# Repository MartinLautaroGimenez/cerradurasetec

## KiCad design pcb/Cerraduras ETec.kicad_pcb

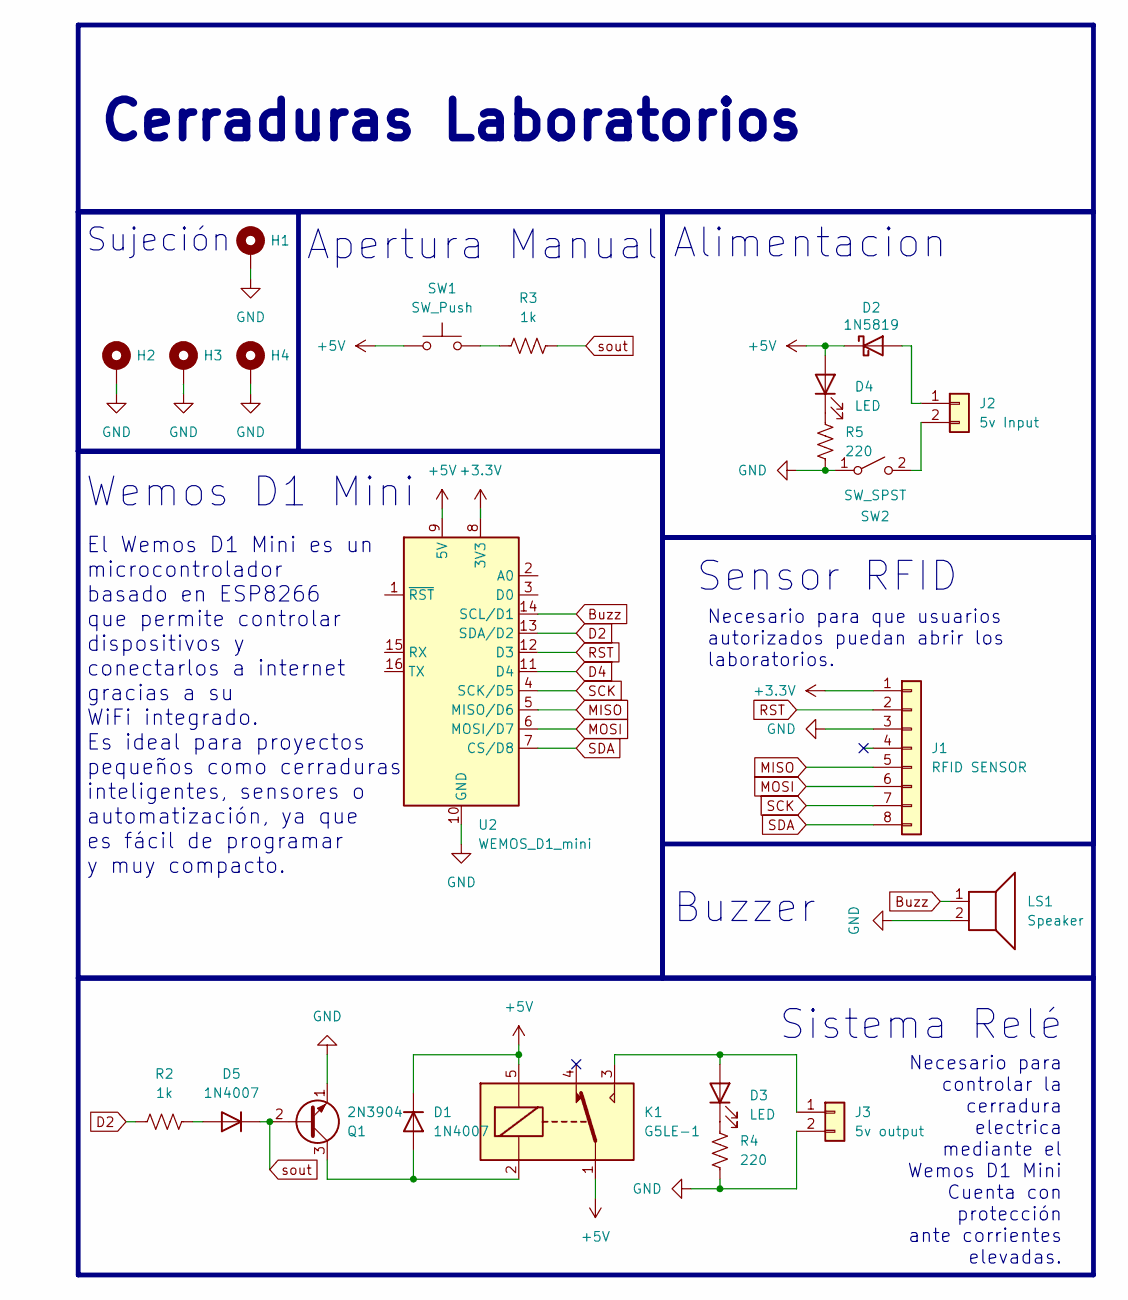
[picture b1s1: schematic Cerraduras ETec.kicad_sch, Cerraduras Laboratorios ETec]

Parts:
D1, D5: 1N4007; D_DO-41_SOD81_P10.16mm_Horizontal
D2: 1N5819; D_DO-41_SOD81_P10.16mm_Horizontal
D3, D4: LED; LED_D3.0mm
H1, H2, H3, H4: MountingHole_Pad; MountingHole_3.5mm_Pad
J1: RFID SENSOR; PinHeader_1x08_P2.54mm_Vertical
J2: 5v Input; TerminalBlock_Phoenix_MKDS-1,5-2_1x02_P5.00mm_Horizontal
J3: 5v output; TerminalBlock_Phoenix_MKDS-1,5-2_1x02_P5.00mm_Horizontal
K1: G5LE-1; Relay_SPDT_Omron-G5LE-1
LS1: Speaker; Buzzer_12x9.5RM7.6
Q1: 2N3904; TO-92_Inline
R2, R3: 1k; R_Axial_DIN0411_L9.9mm_D3.6mm_P15.24mm_Horizontal
R4, R5: 220; R_Axial_DIN0411_L9.9mm_D3.6mm_P15.24mm_Horizontal
SW1: SW_Push; SW_PUSH_6mm_H8mm
SW2: SW_SPST; SW_DIP_SPSTx01_Slide_9.78x4.72mm_W7.62mm_P2.54mm
U2: WEMOS_D1_mini; WEMOS_D1_mini_light

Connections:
+3.3V: J1.1, U2.8 (3V3)
+5V: D1.1 (K), D2.1 (K), D4.2 (A), K1.1, K1.5, SW1.1, U2.9 (5V)
Buzz: LS1.1, U2.14 (SCL/D1)
D2: R2.1, U2.13 (SDA/D2)
D4: U2.11 (D4)
GND: H1.1, H2.1, H3.1, H4.1, J1.3, J3.2, LS1.2, Q1.1 (E), R4.1, R5.1, SW2.1 (A), U2.10 (GND)
MISO: J1.5, U2.5 (MISO/D6)
MOSI: J1.6, U2.6 (MOSI/D7)
unnamed: D1.2 (A), K1.2, Q1.3 (C)
unnamed: D2.2 (A), J2.1
unnamed: D3.2 (A), J3.1, K1.3
unnamed: D3.1 (K), R4.2
unnamed: D4.1 (K), R5.2
unnamed: D5.2 (A), R2.2
unnamed: J2.2, SW2.2 (B)
unnamed: R3.1, SW1.2
RST: J1.2, U2.12 (D3)
SCK: J1.7, U2.4 (SCK/D5)
SDA: J1.8, U2.7 (CS/D8)
sout: D5.1 (K), Q1.2 (B), R3.2

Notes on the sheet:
El Wemos D1 Mini es un microcontrolador basado en ESP8266 que permite controlar dispositivos y conectarlos a internet gracias a su WiFi integrado. Es ideal para proyectos pequeños como cerraduras inteligentes, sensores o automatización, ya que es fácil de programar y muy compacto.
Wemos D1 Mini
Alimentacion
Buzzer
Sujeción
Apertura Manual
Necesario para controlar la cerradura electrica mediante el Wemos D1 Mini Cuenta con protección ante corrientes elevadas.
Necesario para que usuarios autorizados puedan abrir los laboratorios.
Sistema Relé
Sensor RFID
Cerraduras Laboratorios

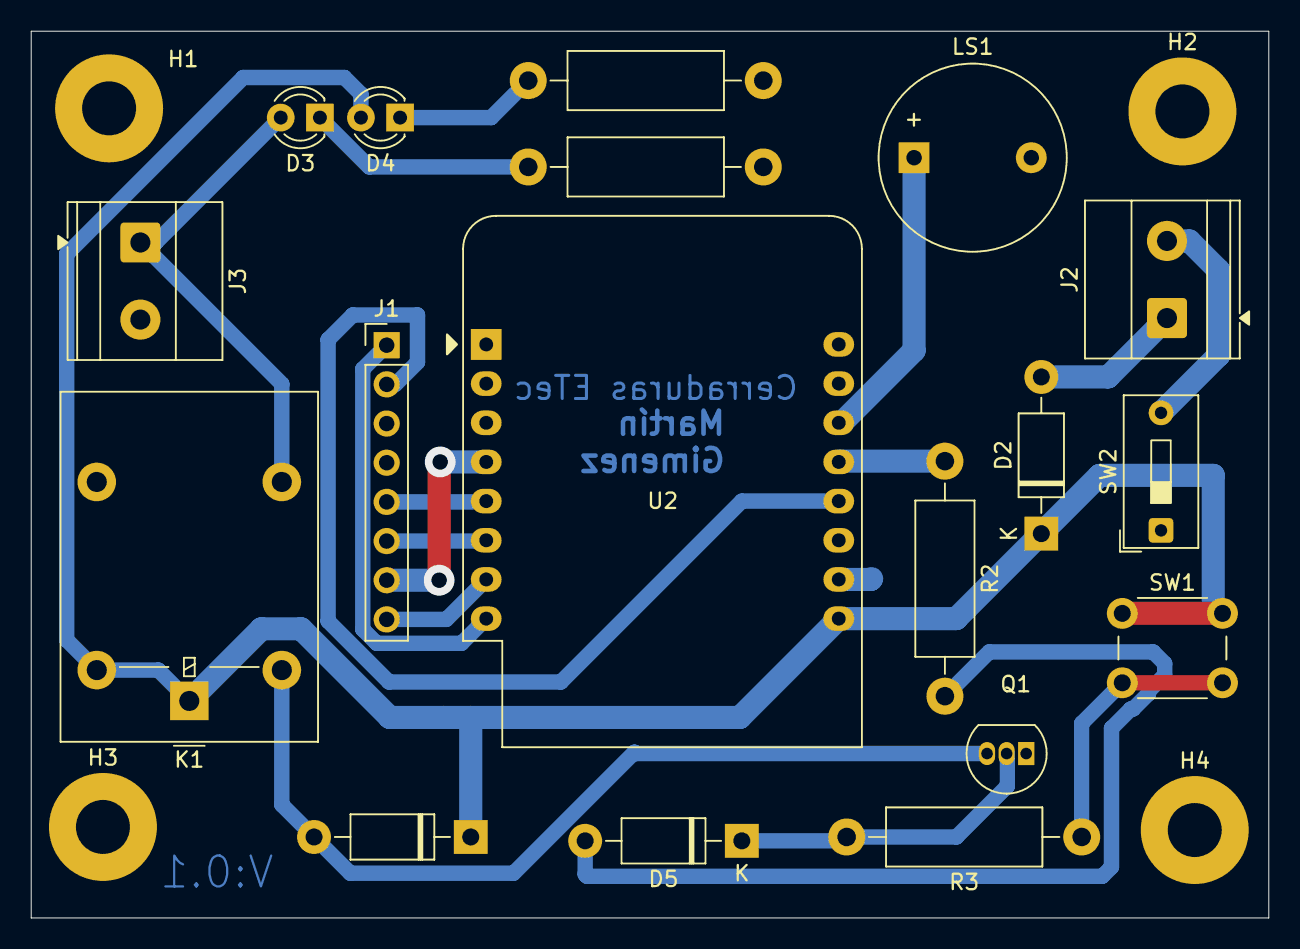
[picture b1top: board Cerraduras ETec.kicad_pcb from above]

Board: 2 copper layers, 80.2 x 57.5 mm, 22 parts (0 on the bottom side), 19 nets.

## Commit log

2025-05-12 Implementación de la interfaz de usuario para la gestión de usuarios RFID, incluyendo la creación, edición y eliminación de usuarios. Se añadió un dashboard con estadísticas de accesos y logs. Se act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
2025-05-12 Añadir archivo de requisitos para la configuración del entorno de Flask y dependencias necesarias.
2025-05-13 Refactor user management and auditing features
    - Converted usuarios.html to use Jinja2 templating with a base layout.
    - Added a new auditing page (auditoria.html) for administrative actions.
    - Created a PDF report template for auditing (auditoria_pdf.html).
    - Introduced a new statistics page (estadisticas.html) with ECharts integration.
    - Added a sidebar partial for consistent navigation across pages.
    - Updated requirements.txt to include WeasyPrint for PDF generation.
2025-05-13 Actualizar texto de la tarjeta de último acceso en el dashboard
2025-07-27 Refactor code structure for improved readability and maintainability
